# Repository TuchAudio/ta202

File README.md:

# TuchAudio 202
Simple, small stereo power amplifier

## Purpose
Simple, no-frills low power (~1.5 W RMS) stage, intended for connection thru the [501 Input Selector Board](../../../ta501) for the so called 'Bedroom Amp'; but could be used independetly as well. 

## Design quirks
LM386-based.

### Stability

### Suggested mods

#### Standalone mode

## Specs

- **Power supply:** 12 V, asymmetrical, max. 400 mA
- **Gain:** 20x (+26 dB) with +46 dB option.
- **Input sensitivity:** 180 mV
- **Input impedance:** 10 kΩ; with optional buffer for standalone operation, ~108 kΩ.
- **Output level and impedance:** 10 Vpp / 8 Ω
- **Output power:** 1.5 W RMS (8 Ω)
- **Frequency response:** TBD
- **Distortion:** TBD

| Harmonic | nominal output | 50 mW |
| -------- | -------------- | ----- |
| 2nd      |  %         |  %           |
| 3rd      |  %         |  %           |
| 4th      |  %         |  %           |

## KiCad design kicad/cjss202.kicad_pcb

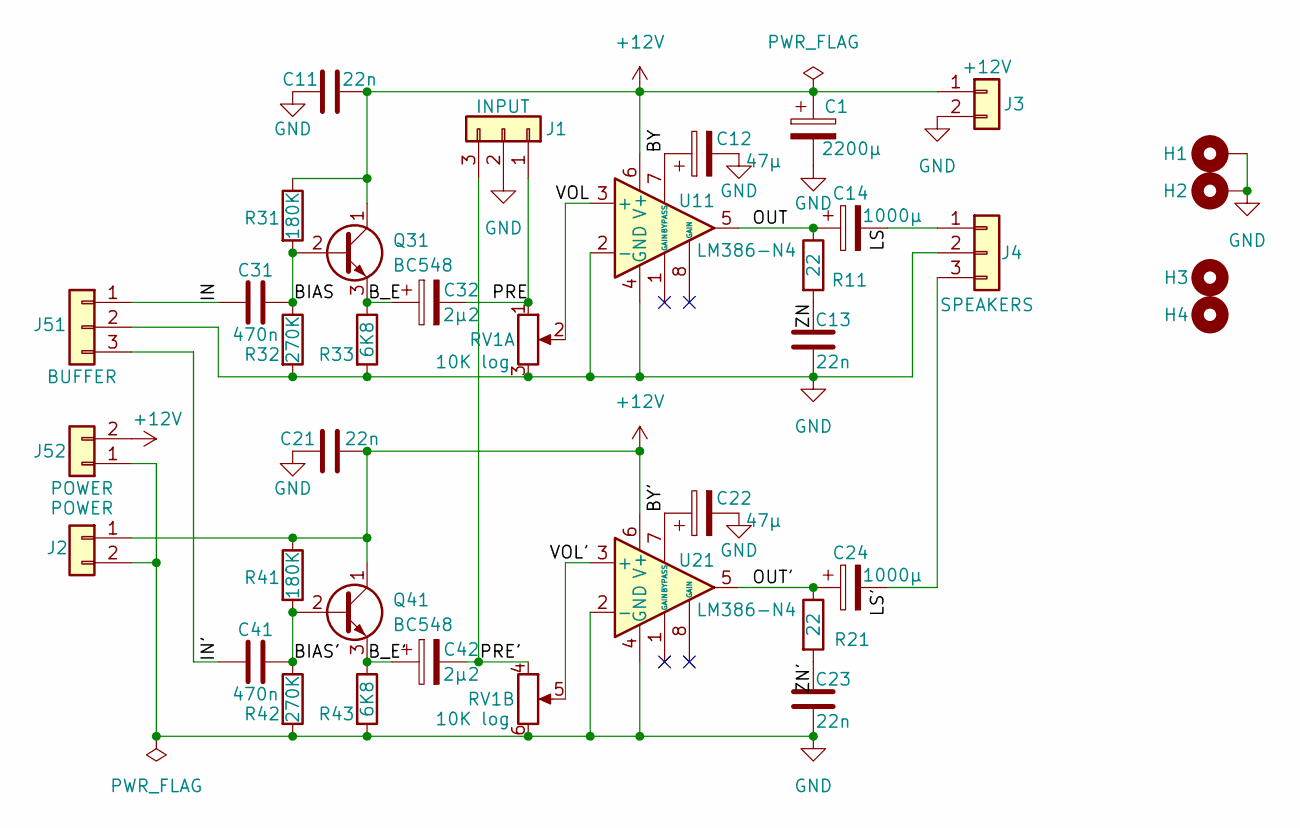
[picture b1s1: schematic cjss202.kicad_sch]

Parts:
C1: 2200µ; CP_Radial_D13.0mm_P5.00mm
C11, C13, C21, C23: 22n; C_Disc_D6.0mm_W2.5mm_P5.00mm
C12, C22: 47µ; CP_Radial_D4.0mm_P1.50mm
C14, C24: 1000µ; CP_Radial_D10.0mm_P5.00mm
C31, C41: 470n; C_Rect_L7.2mm_W3.0mm_P5.00mm_FKS2_FKP2_MKS2_MKP2
C32, C42: 2µ2; CP_Radial_D4.0mm_P1.50mm
H1, H2: MountingHole_Pad; MountingHole_3.2mm_M3_DIN965_Pad
H3, H4: MountingHole; MountingHole_3.2mm_M3
J1: INPUT; PinHeader_1x03_P2.54mm_Horizontal
J2, J52: POWER; PinHeader_1x02_P2.54mm_Horizontal
J3: +12V; PinHeader_1x02_P2.54mm_Vertical
J4: SPEAKERS; PinHeader_1x03_P2.54mm_Vertical
J51: BUFFER; PinHeader_1x03_P2.54mm_Horizontal
Q31, Q41: BC548; TO-92_Inline
R11, R21: 22; R_Axial_DIN0207_L6.3mm_D2.5mm_P10.16mm_Horizontal
R31, R41: 180K; R_Axial_DIN0207_L6.3mm_D2.5mm_P10.16mm_Horizontal
R32, R42: 270K; R_Axial_DIN0207_L6.3mm_D2.5mm_P10.16mm_Horizontal
R33, R43: 6K8; R_Axial_DIN0207_L6.3mm_D2.5mm_P10.16mm_Horizontal
RV1: 10K log; Potentiometer_Alps_225G_Dual_Horizontal
U11, U21: LM386-N4; DIP-8_W7.62mm

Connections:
+12V: C1.1, C11.2, C21.2, J2.1, J3.1, J52.2, Q31.1 (C), Q41.1 (C), R31.1, R41.1, U11.6 (V+), U21.6 (V+)
/BIAS: C31.2, Q31.2 (B), R31.2, R32.1
/BIAS': C41.2, Q41.2 (B), R41.2, R42.1
/BY: C12.1, U11.7 (BYPASS)
/BY': C22.1, U21.7 (BYPASS)
/B_E: C32.1, Q31.3 (E), R33.1
/B_E': C42.1, Q41.3 (E), R43.1
/IN: C31.1, J51.1
/IN': C41.1, J51.3
/LS: C14.2, J4.1
/LS': C24.2, J4.3
/OUT: C14.1, R11.1, U11.5
/OUT': C24.1, R21.1, U21.5
/PRE: C32.2, J1.1, RV1.1
/PRE': C42.2, J1.3, RV1.4
/VOL: RV1.2, U11.3 (+)
/VOL': RV1.5, U21.3 (+)
/ZN: C13.1, R11.2
/ZN': C23.1, R21.2
GND: C1.2, C11.1, C12.2, C13.2, C21.1, C22.2, C23.2, H1.1, H2.1, J1.2, J2.2, J3.2, J4.2, J51.2, J52.1, R32.2, R33.2, R42.2, R43.2, RV1.3, RV1.6, U11.2 (-), U11.4 (GND), U21.2 (-), U21.4 (GND)

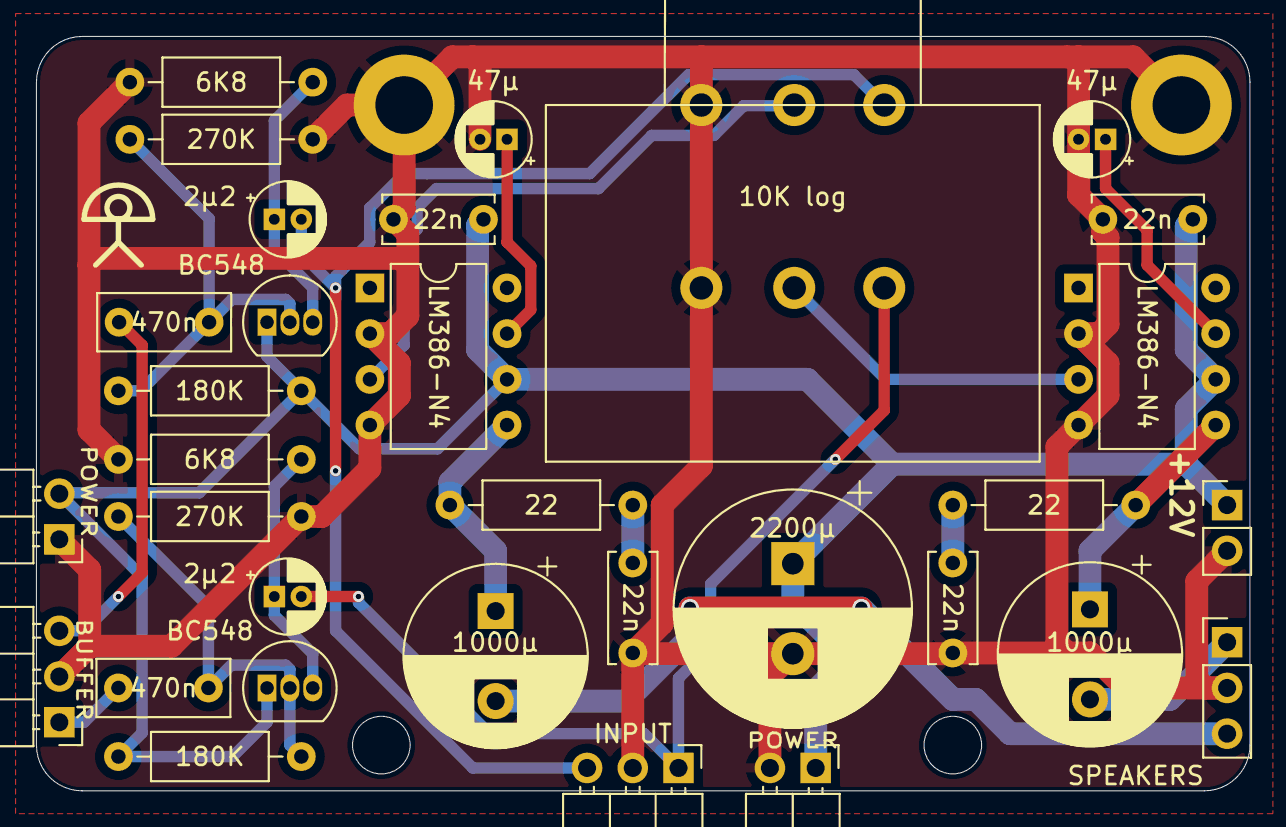
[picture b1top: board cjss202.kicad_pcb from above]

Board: 2 copper layers, 67.4 x 41.9 mm, 36 parts (0 on the bottom side), 20 nets.

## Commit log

2025-09-09 stub
2025-09-09 fix output level and input impedance
2025-11-08 add KiCAD files
2025-11-12 add pics
2025-11-24 links and design base
